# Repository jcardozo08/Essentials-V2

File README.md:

# Essentials V2

Segunda versão da placa Essentials, redesenhada para o **ESP32-S3**. Ela é composta por **dois módulos**: a placa principal e uma placa de comunicação separada para o **LoRa e o GPS**, que pode ser posicionada em outro lugar do foguete, longe de interferências.

## Destaques

- **ESP32-S3-DevKitC** como microcontrolador
- **4 canais de ignição** (IGN1–IGN4) para eventos de recuperação, com MOSFETs de potência IRLZ44N e drivers SI2300
- Módulo de comunicação com rádio LoRa **E32-915T20D** e conector para GPS
- Conector para IMU (GY-91 / ICM-20948), LED RGB de status, botão de reset e pontos de teste
- Firmware: [FlightCode](https://github.com/jcardozo08/FlightCode) / [FlightComputerRTOS](https://github.com/jcardozo08/FlightComputerRTOS)

| Topo | Base |
|:---:|:---:|
|  |  |

## Arquivos

- `Essentials V2.kicad_sch`: esquemático ([ver em SVG](images/schematic.svg))
- `Essentials V2.kicad_pcb`: layout das duas placas ([ver em SVG](images/layout.svg))
- `Essentials V2.step`: modelo 3D

**Ferramenta:** KiCad

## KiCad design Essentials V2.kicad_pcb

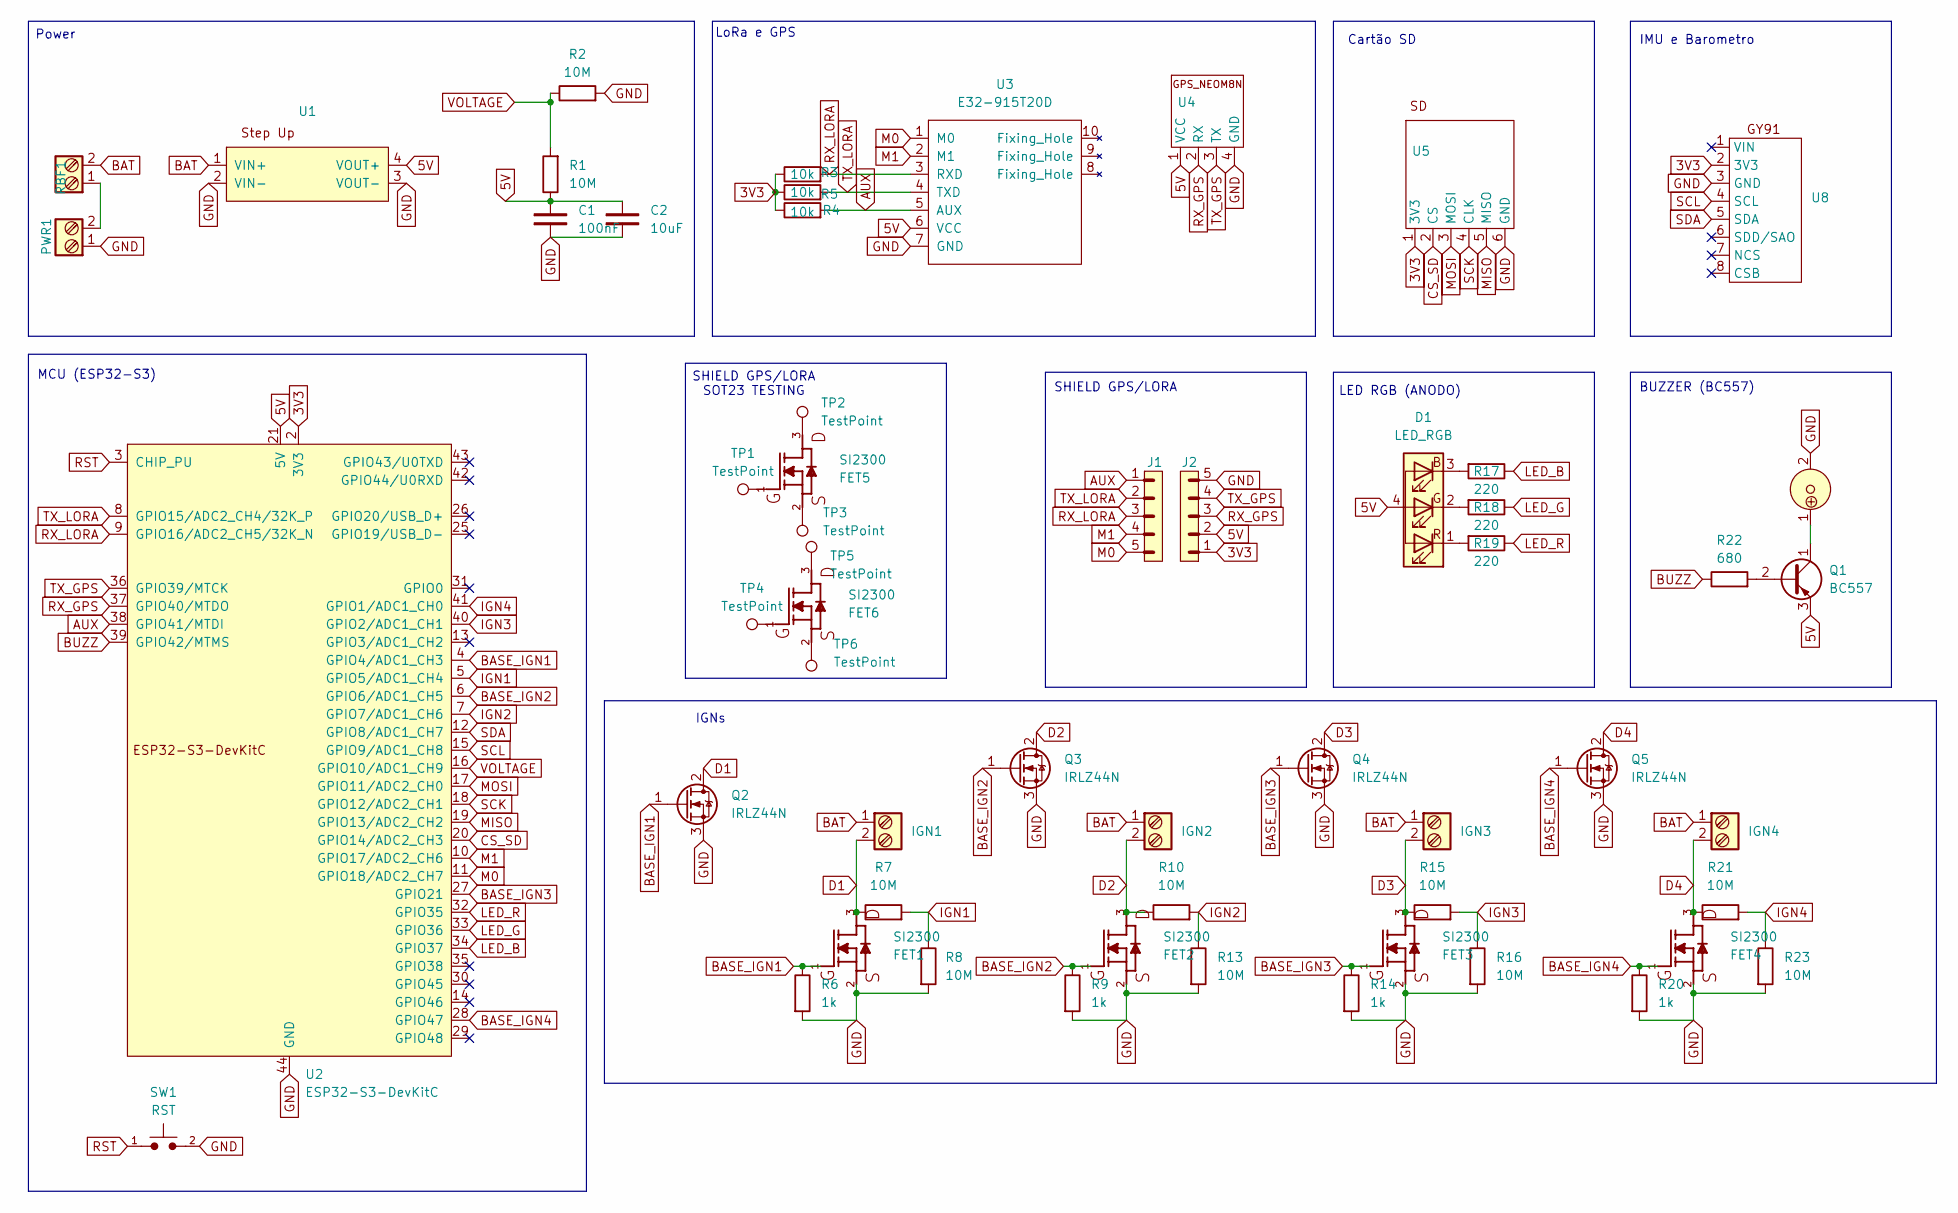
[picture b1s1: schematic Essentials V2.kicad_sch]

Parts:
B1: IGN1; Borne 2 Vias
B2: IGN2; Borne 2 Vias
B3: IGN3; Borne 2 Vias
B4: IGN4; Borne 2 Vias
C1: 100nF; C_0805_2012Metric_Pad1.18x1.45mm_HandSolder
C2: 10uF; C_0805_2012Metric_Pad1.18x1.45mm_HandSolder
D1: LED_RGB
FET1, FET2, FET3, FET4, FET5, FET6: SI2300; SOT23_SI2300
J1, J2: PINHD_1x5_Male; PinHeader_1x05_P2.54mm_Vertical
PWR1: Borne_2_vias; Borne 2 Vias
Q1: BC557; TO-92_Inline
Q2, Q3, Q4, Q5: IRLZ44N; TO-220-3_Vertical
R1, R2, R7, R8, R10, R13, R15, R16, R21, R23: 10M; R_0805_2012Metric_Pad1.20x1.40mm_HandSolder
R3, R4, R5: 10k; R_0805_2012Metric_Pad1.20x1.40mm_HandSolder
R6, R9, R14, R20: 1k; R_0805_2012Metric_Pad1.20x1.40mm_HandSolder
R17, R18, R19: 220; R_0805_2012Metric_Pad1.20x1.40mm_HandSolder
R22: 680; R_0805_2012Metric_Pad1.20x1.40mm_HandSolder
RBF1: Borne_2_vias; Borne 2 Vias
SW1: RST; SW_PUSH_6mm
TP1, TP2, TP3, TP4, TP5, TP6: TestPoint
U1: Step Up
U2: ESP32-S3-DevKitC
U3: E32-915T20D; E32-xxxT20D
U4: GPS_NeoM8N
U5: MicroSD_Module_3.3V
U7: Buzzer
U8: GY-91_Module

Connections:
3V3: J2.1, R3.1, R4.1, R5.1, U2.1 (3V3), U2.2 (3V3), U5.1 (3V3), U8.2 (3V3); also elsewhere on the board
5V: C1.2, C2.2, D1.4 (GA), J2.2, Q1.3 (E), R1.1, U1.4 (VOUT+), U2.21 (5V), U3.6 (VCC), U4.1 (VCC); also elsewhere on the board
AUX: J1.1, R5.2, U2.38 (GPIO41/MTDI), U3.5 (AUX); also elsewhere on the board
BASE_IGN1: FET1.1, Q2.1 (G), R6.1, U2.4 (GPIO4/ADC1_CH3)
BASE_IGN2: FET2.1, Q3.1 (G), R9.1, U2.6 (GPIO6/ADC1_CH5)
BASE_IGN3: FET3.1, Q4.1 (G), R14.1, U2.27 (GPIO21)
BASE_IGN4: FET4.1, Q5.1 (G), R20.1, U2.28 (GPIO47)
BAT: B1.1, B2.1, B3.1, B4.1, RBF1.2, U1.1 (VIN+)
BUZZ: R22.1, U2.39 (GPIO42/MTMS)
CS_SD: U2.20 (GPIO14/ADC2_CH3), U5.2 (CS)
D1: B1.2, FET1.3, Q2.2 (D), R7.1
D2: B2.2, FET2.3, Q3.2 (D), R10.1
D3: B3.2, FET3.3, Q4.2 (D), R15.1
D4: B4.2, FET4.3, Q5.2 (D), R21.1
GND: C1.1, C2.1, FET1.2, FET2.2, FET3.2, FET4.2, J2.5, PWR1.1, Q2.3 (S), Q3.3 (S), Q4.3 (S), Q5.3 (S), R2.2, R6.2, R8.2, R9.2, R13.2, R14.2, R16.2, R20.2, R23.2, SW1.2, U1.2 (VIN-), U1.3 (VOUT-), U2.22 (GND), U2.23 (GND), U2.24 (GND), U2.44 (GND), U3.7 (GND), U4.4 (GND), U5.6 (GND), U7.2, U8.3 (GND); also elsewhere on the board
IGN1: R7.2, R8.1, U2.5 (GPIO5/ADC1_CH4)
IGN2: R10.2, R13.1, U2.7 (GPIO7/ADC1_CH6)
IGN3: R15.2, R16.1, U2.40 (GPIO2/ADC1_CH1)
IGN4: R21.2, R23.1, U2.41 (GPIO1/ADC1_CH0)
LED_B: R17.1, U2.34 (GPIO37)
LED_G: R18.1, U2.33 (GPIO36)
LED_R: R19.1, U2.32 (GPIO35)
M0: J1.5, U2.11 (GPIO18/ADC2_CH7), U3.1 (M0); also elsewhere on the board
M1: J1.4, U2.10 (GPIO17/ADC2_CH6), U3.2 (M1); also elsewhere on the board
MISO: U2.19 (GPIO13/ADC2_CH2), U5.5 (MISO)
MOSI: U2.17 (GPIO11/ADC2_CH0), U5.3 (MOSI)
unnamed: D1.3 (BK), R17.2
unnamed: D1.2 (GK), R18.2
unnamed: D1.1 (RK), R19.2
unnamed: FET5.1, TP1.1
unnamed: FET5.2, TP3.1
unnamed: FET5.3, TP2.1
unnamed: FET6.1, TP4.1
unnamed: FET6.2, TP6.1
unnamed: FET6.3, TP5.1
unnamed: PWR1.2, RBF1.1
unnamed: Q1.2 (B), R22.2
unnamed: Q1.1 (C), U7.1
RST: SW1.1, U2.3 (CHIP_PU)
RX_GPS: J2.3, U2.37 (GPIO40/MTDO), U4.2 (RX); also elsewhere on the board
RX_LORA: J1.3, R3.2, U2.9 (GPIO16/ADC2_CH5/32K_N), U3.3 (RXD); also elsewhere on the board
SCK: U2.18 (GPIO12/ADC2_CH1), U5.4 (CLK)
SCL: U2.15 (GPIO9/ADC1_CH8), U8.4 (SCL)
SDA: U2.12 (GPIO8/ADC1_CH7), U8.5 (SDA)
TX_GPS: J2.4, U2.36 (GPIO39/MTCK), U4.3 (TX); also elsewhere on the board
TX_LORA: J1.2, R4.2, U2.8 (GPIO15/ADC2_CH4/32K_P), U3.4 (TXD); also elsewhere on the board
VOLTAGE: R1.2, R2.1, U2.16 (GPIO10/ADC1_CH9)

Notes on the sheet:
LoRa e GPS
SHIELD GPS/LORA SOT23 TESTING
IMU e Barometro
Power
LED RGB (ANODO)
IGNs
BUZZER (BC557)
Cartão SD
SHIELD GPS/LORA
MCU (ESP32-S3)

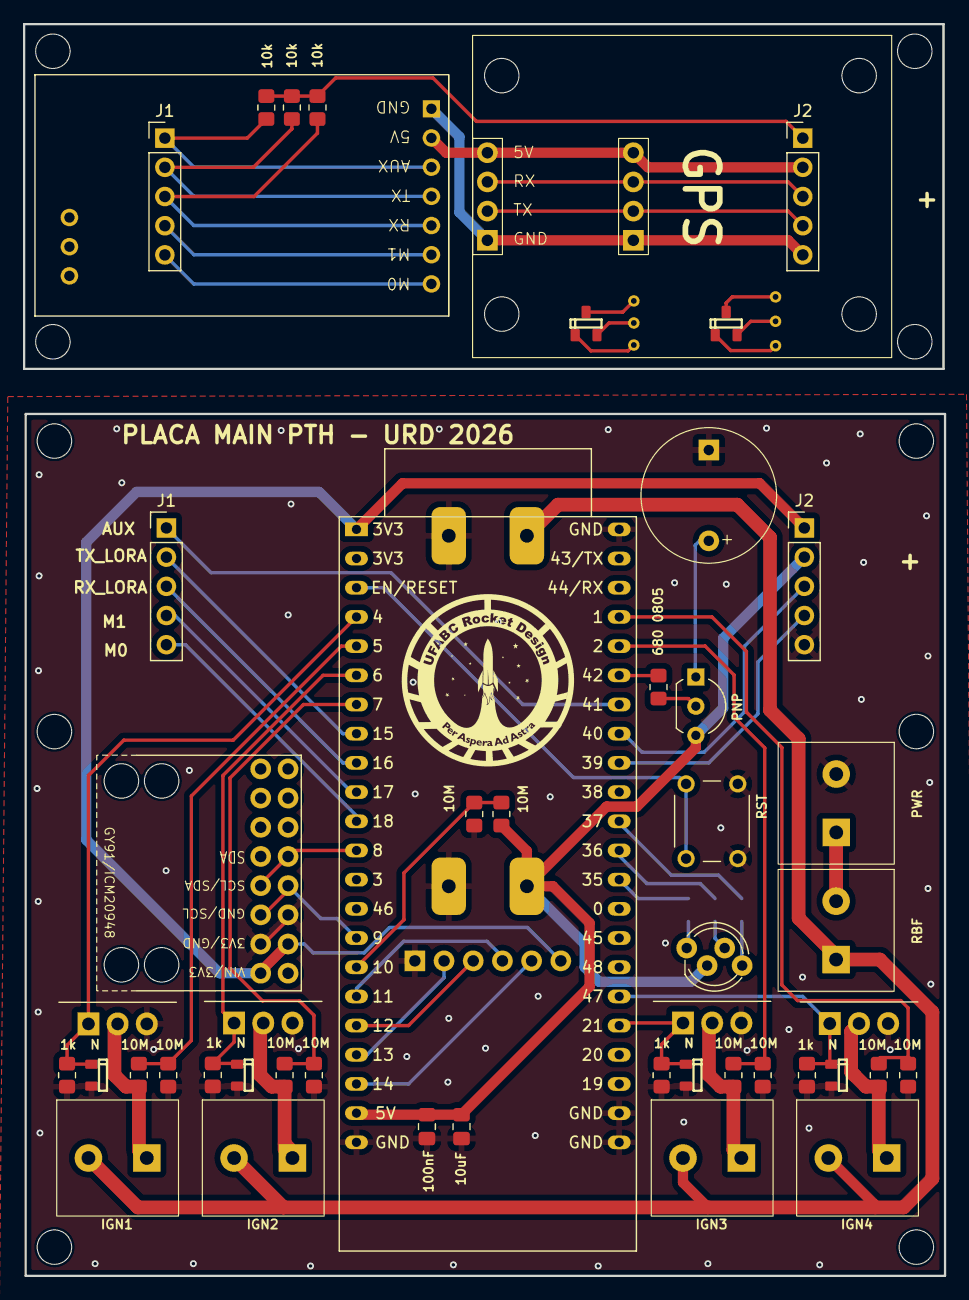
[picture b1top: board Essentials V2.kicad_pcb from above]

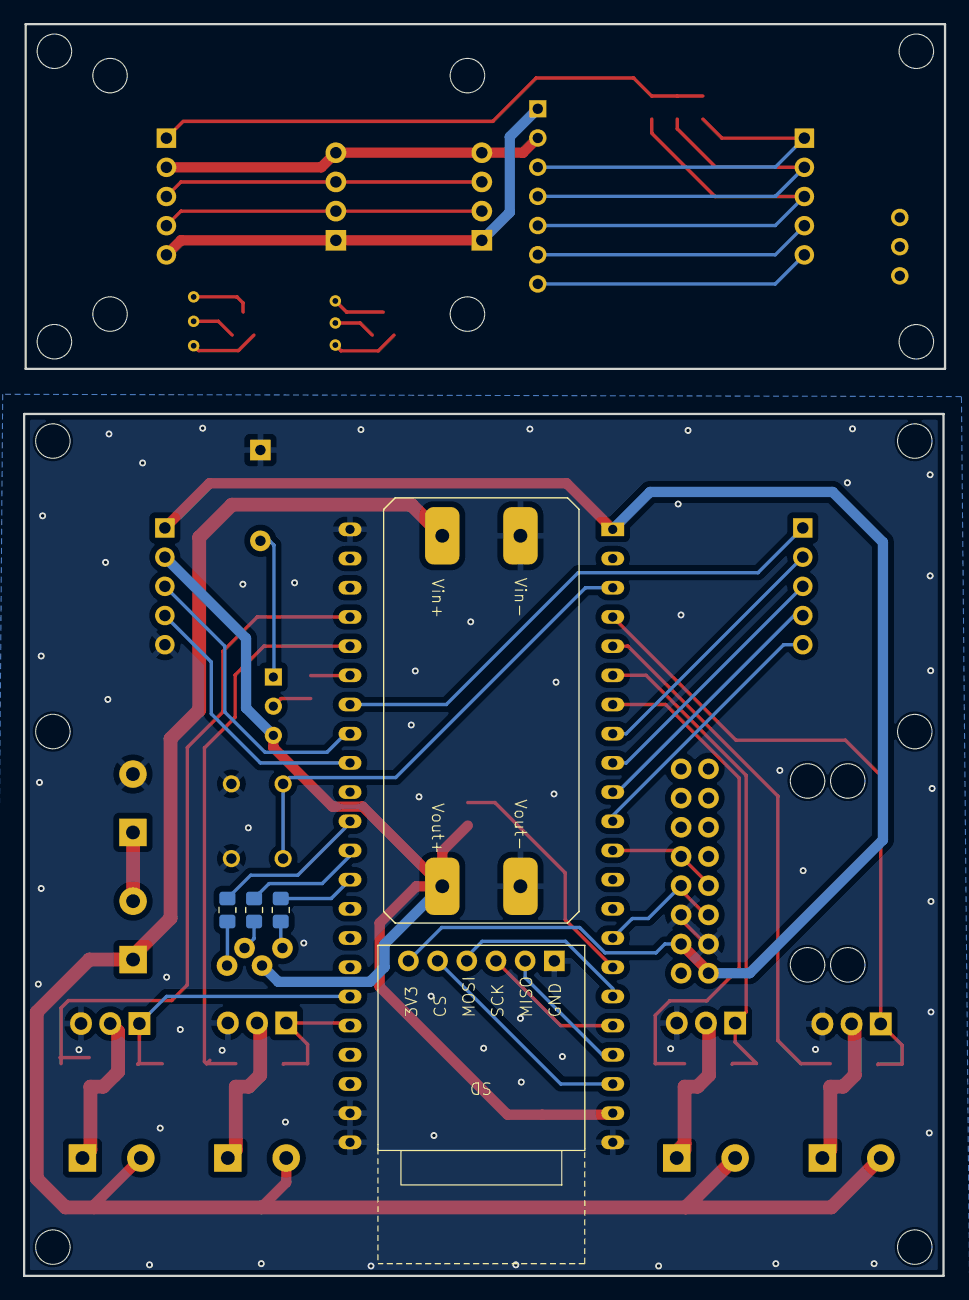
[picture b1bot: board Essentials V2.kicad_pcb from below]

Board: 2 copper layers, 80.1 x 108.9 mm, 70 parts (5 on the bottom side), 47 nets.

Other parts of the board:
G1: LOGO; LogoRocket
J1#2, J2#2: PINHD_1x5_Male; PinHeader_1x05_P2.54mm_Vertical
NPTH1, NPTH1#2, NPTH2, NPTH2#2, NPTH3, NPTH3#2, NPTH3#3, NPTH3#4, NPTH3#5, NPTH4: (no value)

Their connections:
3V3: J2#2.1; also elsewhere on the board
5V: J2#2.2; also elsewhere on the board
AUX: J1#2.1; also elsewhere on the board
GND: J2#2.5; also elsewhere on the board
M0: J1#2.5; also elsewhere on the board
M1: J1#2.4; also elsewhere on the board
RX_GPS: J2#2.3; also elsewhere on the board
RX_LORA: J1#2.3; also elsewhere on the board
TX_GPS: J2#2.4; also elsewhere on the board
TX_LORA: J1#2.2; also elsewhere on the board
